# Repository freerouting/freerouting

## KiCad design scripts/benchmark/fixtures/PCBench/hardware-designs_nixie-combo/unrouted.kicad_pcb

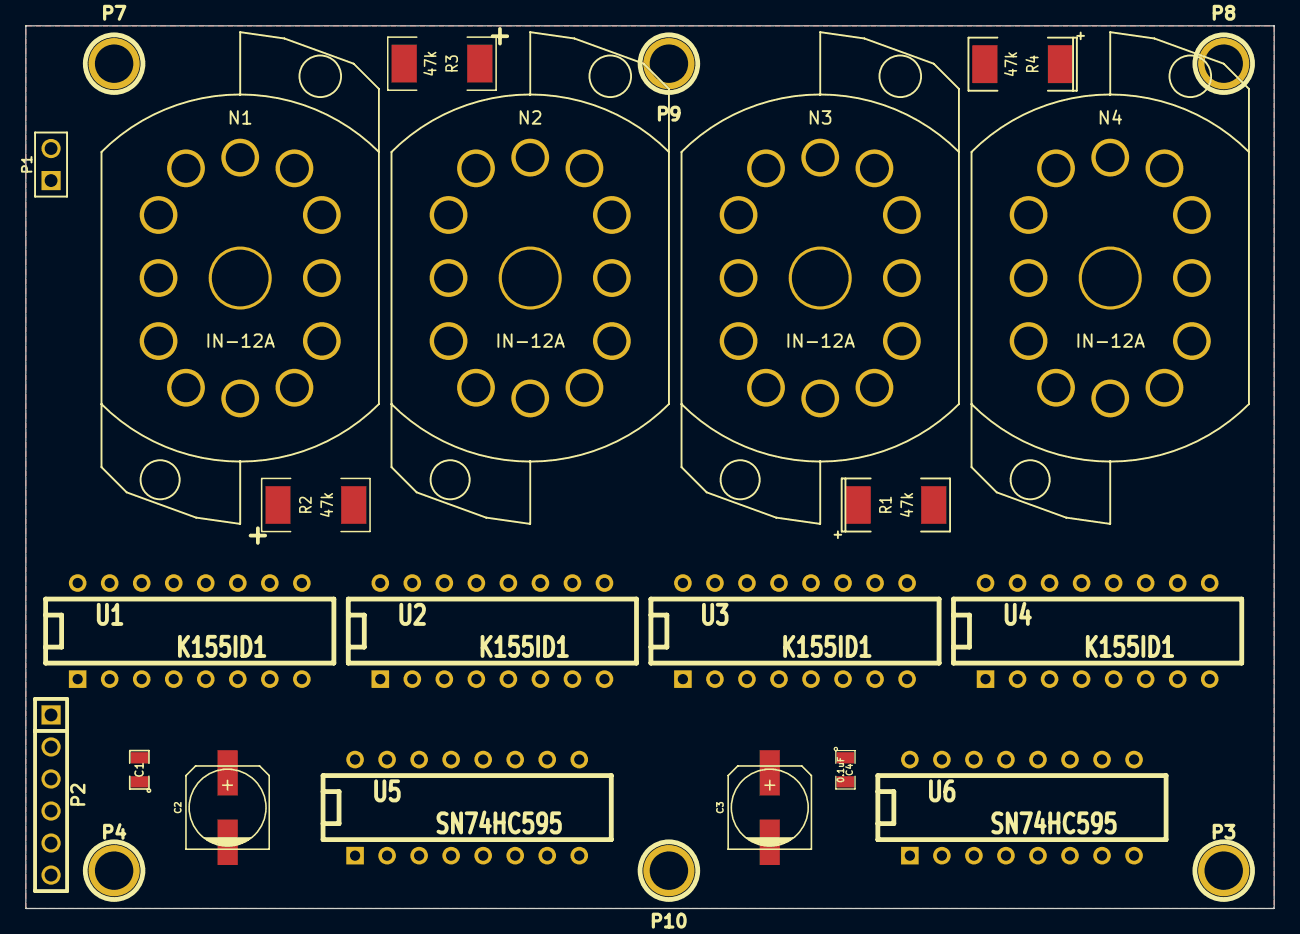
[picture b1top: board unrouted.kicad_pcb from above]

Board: 2 copper layers, 99.0 x 70.0 mm, 27 parts (1 on the bottom side), 67 nets, no tracks yet.

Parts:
C1, C4: 0.1uF; SM0805
C2, C3: 100uF; c_elec_6.3x7.7
N1, N2, N3, N4: IN-12A; IN-12A-SOCKET
Noname_1: LOGO_SNOWCAP_BACK
P1: CONN_2; PIN_ARRAY_2X1
P2: CONN_6; PIN_ARRAY-6X1
P3, P4, P7, P8, P9, P10: CONN_1; 1pin
R1, R2, R3, R4: 47k; SM2512
U1, U2, U3, U4: K155ID1; DIP-16__300
U5, U6: SN74HC595; DIP-16__300

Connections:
+3.3V: C1.1, C2.1, C3.1, C4.1, P2.5, U1.5, U2.5, U3.5, U4.5, U5.10, U5.16, U6.10, U6.16
/a0: N1.2, U1.16
/a1: N1.11, U1.15
/a2: N1.10, U1.8
/a3: N1.9, U1.9
/a4: N1.8, U1.13
/a5: N1.7, U1.14
/a6: N1.6, U1.11
/a7: N1.5, U1.10
/a8: N1.4, U1.1
/a9: N1.3, U1.2
/b0: N2.2, U2.16
/b1: N2.11, U2.15
/b2: N2.10, U2.8
/b3: N2.9, U2.9
/b4: N2.8, U2.13
/b5: N2.7, U2.14
/b6: N2.6, U2.11
/b7: N2.5, U2.10
/b8: N2.4, U2.1
/b9: N2.3, U2.2
/c0: N3.2, U3.16
/c1: N3.11, U3.15
/c2: N3.10, U3.8
/c3: N3.9, U3.9
/c4: N3.8, U3.13
/c5: N3.7, U3.14
/c6: N3.6, U3.11
/c7: N3.5, U3.10
/c8: N3.4, U3.1
/c9: N3.3, U3.2
/d0: N4.2, U4.16
/d1: N4.11, U4.15
/d2: N4.10, U4.8
/d3: N4.9, U4.9
/d4: N4.8, U4.13
/d5: N4.7, U4.14
/d6: N4.6, U4.11
/d7: N4.5, U4.10
/d8: N4.4, U4.1
/d9: N4.3, U4.2
GND: C1.2, C2.2, C3.2, C4.2, P1.1, P2.2, P3.1, P4.1, P7.1, P8.1, P9.1, P10.1, U1.12, U2.12, U3.12, U4.12, U5.8, U5.13, U6.8, U6.13
HT: P1.2, R1.2, R2.2, R3.2, R4.2
unnamed: N4.1, R4.1
unnamed: U4.7, U6.6
unnamed: U4.4, U6.7
unnamed: U4.3, U6.4
unnamed: U3.7, U6.2
unnamed: U3.6, U6.1
unnamed: U3.4, U6.3
unnamed: N1.1, R2.1
unnamed: N2.1, R3.1
unnamed: N3.1, R1.1
unnamed: U3.3, U6.15
unnamed: U4.6, U6.5
unnamed: U5.9, U6.14
unnamed: P2.4, U5.12, U6.12
unnamed: P2.3, U5.11, U6.11
unnamed: P2.1, U5.14
unnamed: U2.4, U5.7
unnamed: U2.7, U5.6
unnamed: U2.6, U5.5
unnamed: U2.3, U5.4
unnamed: U1.4, U5.3
unnamed: U1.7, U5.2
unnamed: U1.6, U5.1
unnamed: U1.3, U5.15

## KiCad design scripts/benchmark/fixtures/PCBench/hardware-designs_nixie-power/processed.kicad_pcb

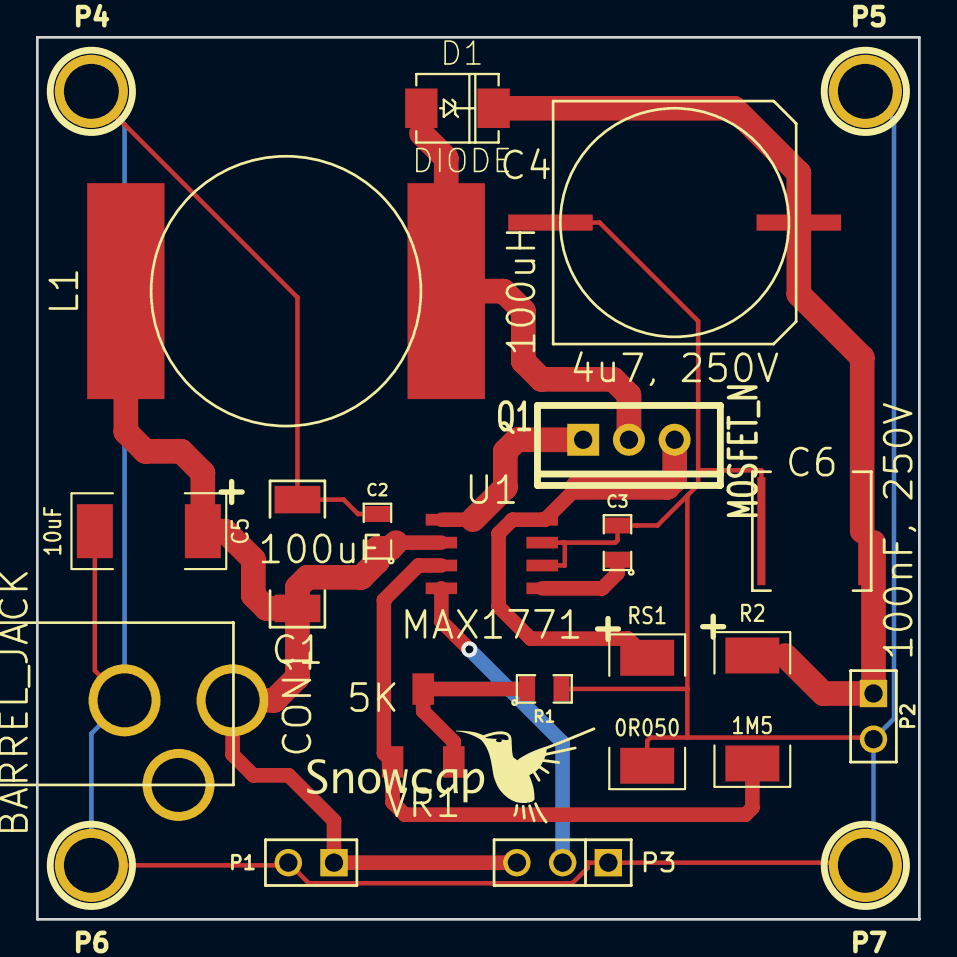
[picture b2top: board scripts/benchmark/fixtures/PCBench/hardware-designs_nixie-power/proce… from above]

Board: 2 copper layers, 49.0 x 49.0 mm, 24 parts (1 on the bottom side), 10 nets.

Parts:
C1: 100uF; SM2917
C2, C3: 100nF; SM0805
C4: 4u7, 250V; c_elec_13.5x13.8
C5: 10uF; SM2512
C6: 100nF, 250V; SM2420_fc1
CON1: BARREL_JACK; BARREL_JACK-PJ-002AH
D1: DIODE; DO214
L1: 100uH; UNI-PAC4B
Noname_1: LOGO_SNOWCAP_BACK
Noname_2: LOGO_SNOWCAP_FRONT
P1, P2: CONN_2; PIN_ARRAY_2X1
P3: CONN_3; PIN_ARRAY_3X1
P4, P5, P6, P7: CONN_1; 1pin
Q1: MOSFET_N; TO220_VERT_GDS
R1: 10K; SM0805
R2: 1M5; SM2512
RS1: 0R050; SM2512
U1: MAX1771; SOIC-8
VR1: 5K; 3314S-TRIMPOT

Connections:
FB: R2.2, U1.3, VR1.1
GND: C1.2, C2.2, C3.2, C4.2, C5.2, C6.2, CON1.2, P1.2, P2.2, P3.1, P4.1, P5.1, P6.1, P7.1, R1.2, RS1.2, U1.6, U1.7
unnamed: C3.1, U1.5
unnamed: C1.1, C2.1, C5.1, CON1.1, L1.1, P1.1, P3.3, U1.2
unnamed: Q1.G, U1.1
unnamed: C4.1, C6.1, D1.2, P2.1, R2.1
unnamed: Q1.S, RS1.1, U1.8
unnamed: P3.2, U1.4
unnamed: D1.1, L1.2, Q1.D
unnamed: R1.1, VR1.2, VR1.3

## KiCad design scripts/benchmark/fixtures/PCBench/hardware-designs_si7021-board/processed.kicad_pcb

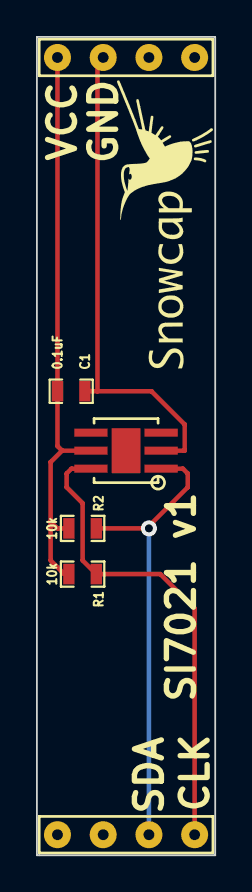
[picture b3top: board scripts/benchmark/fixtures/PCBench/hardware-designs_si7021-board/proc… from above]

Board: 2 copper layers, 9.9 x 45.5 mm, 6 parts (0 on the bottom side), 4 nets.

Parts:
C1: 0.1uF; SM0603_Capa
Noname_1: LOGO_SNOWCAP_FRONT
R1, R2: 10k; SM0603_Resistor
U1: SHIELD_I2C
U2: SI7021

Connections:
GND: C1.2, U1.2, U2.2
unnamed: R1.2, U1.8, U2.6
unnamed: R2.2, U1.7, U2.1
VCC: C1.1, R1.1, R2.1, U1.1, U2.5

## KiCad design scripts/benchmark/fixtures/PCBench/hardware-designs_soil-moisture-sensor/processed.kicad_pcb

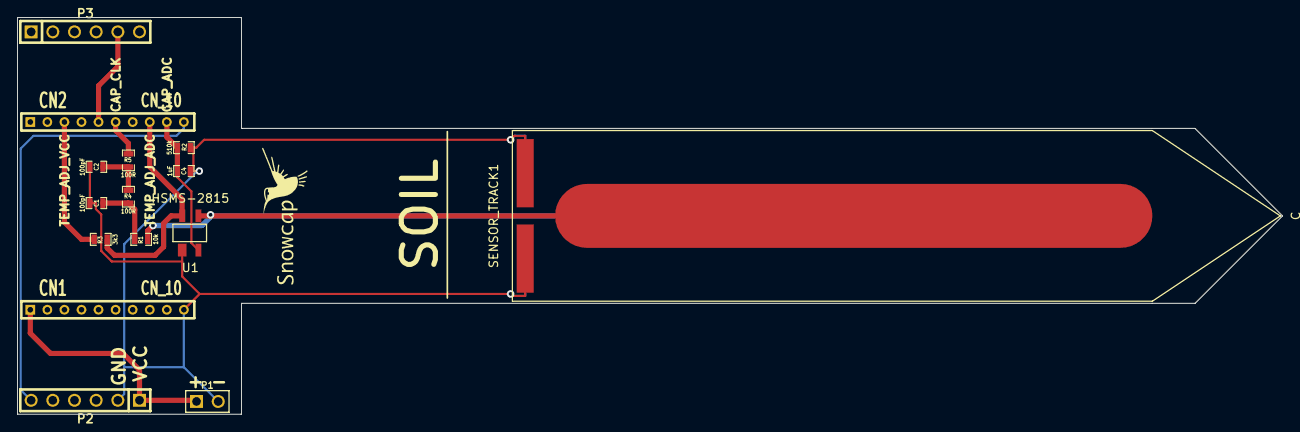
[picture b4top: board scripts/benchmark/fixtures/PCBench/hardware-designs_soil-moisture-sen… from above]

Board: 2 copper layers, 148.2 x 46.5 mm, 16 parts (0 on the bottom side), 11 nets.

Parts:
C1, C2: 100pF; SM0603_Capa
C4: 1uF; SM0603_Capa
CN1, CN2: CN_10; CONN-10-2MM
Noname_1: LOGO_SNOWCAP_FRONT
P1: CONN_2; PIN_ARRAY_2X1
P2, P3: CN_6; PIN_ARRAY-6X1
R1: 10k; SM0603_Resistor
R2: 510k; SM0603_Resistor
R3: 3k3; SM0603_Resistor
R4, R5: 100R; SM0603_Resistor
SENSOR_TRACK1: C; SOIL_SENSOR_CAPACITIVE
U1: HSMS-2815

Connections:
+3.3V: CN1.1, P1.1, P2.1
/CAP_ADC: C4.1, CN2.9, R2.1, U1.2
/CAP_CLK: CN2.6, R5.2
/TEMP_ADJ_ADC: CN2.8, R3.1, U1.3
/TEMP_ADJ_VCC: CN2.3, R3.2
/V_MEASURE1: CN2.10, P2.6
/V_MEASURE2: CN2.5, P3.5
GND: C1.1, C2.1, C4.2, CN1.10, P1.2, P2.2, R2.2, SENSOR_TRACK1.2, U1.1
unnamed: C2.2, R4.2, R5.1
unnamed: C1.2, R1.2, R4.1
unnamed: R1.1, SENSOR_TRACK1.1, U1.4
